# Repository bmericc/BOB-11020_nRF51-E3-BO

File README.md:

View this project on [CADLAB.io](https://cadlab.io/node/798). 

## E3-nRf51-BO

This is a breakout board for the popular inexpensive nRF51822 modules with 
dual 2x9 1.27 mm pin headers.

This product is jointly developed by [Explore Embedded][1] and [electronut.in][2].

[1]: https://www.exploreembedded.com/
[2]: http://electronut.in/

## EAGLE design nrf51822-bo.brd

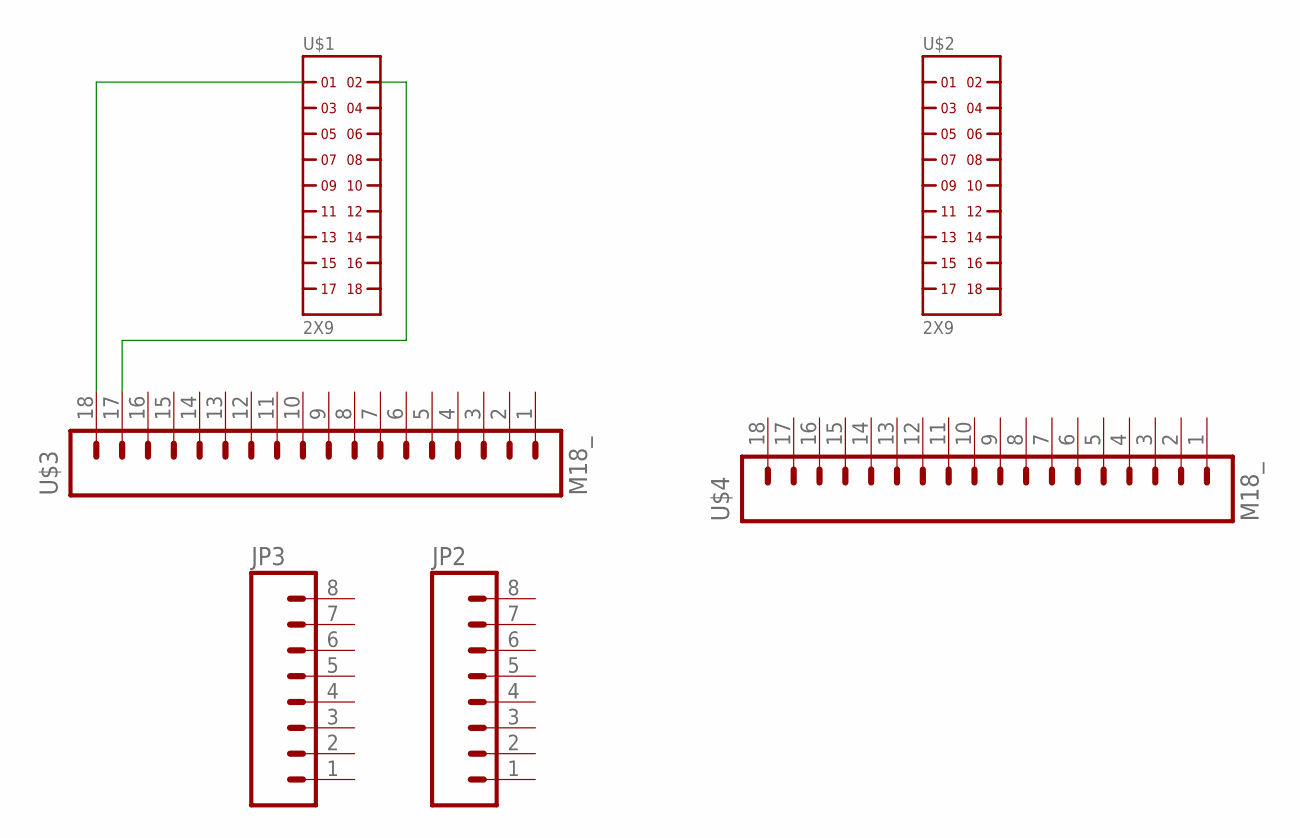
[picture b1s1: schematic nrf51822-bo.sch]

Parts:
JP2, JP3: M08; 1X08_PIN1_NO_SILK
U$1, U$2: 2X9
U$3, U$4: M18_; 1X18

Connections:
unnamed: U$1.1, U$3.18
unnamed: U$1.2, U$3.17

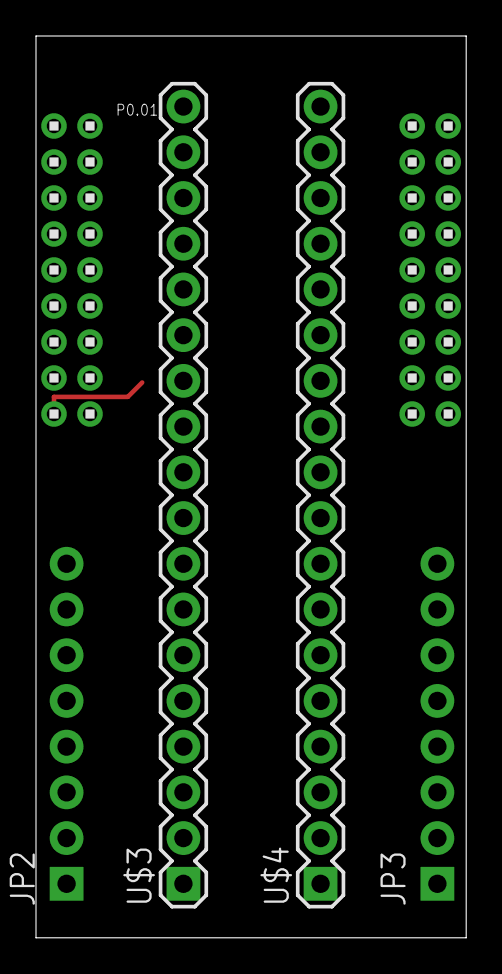
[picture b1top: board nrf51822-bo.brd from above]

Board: 2 copper layers, 23.9 x 50.1 mm, 6 parts (0 on the bottom side), 2 nets.

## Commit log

2015-08-13 Added Files
2015-08-18 ADDED NEW FILES
2015-08-19 Corrected File
2015-08-19 corrected files
2015-08-20 added logo
2015-09-07 Changed name
2015-09-08 added README
2015-09-08 added README with images
2015-09-08 removed EAGLE files
2015-09-09 added board name and version
2015-09-09 Final
2017-06-24 gerber
2018-03-27 Backlink to CADLAB.io has been added.

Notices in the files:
parts and their libraries:
SparkFun-Connectors: Licensing: Creative Commons ShareAlike 4.0 International - https://creativecommons.org/licenses/by-sa/4.0
